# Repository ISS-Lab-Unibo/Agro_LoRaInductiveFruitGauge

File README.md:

# Agro LoRa Inductive Fruit Gauge

An open-source, low-cost and low-power LoRaWAN sensor node for continuous, non-destructive monitoring of fruit growth directly on the tree, together with the high-resolution inductive fruit gauges (*pliers*) it reads.

## Overview

Fruits shrink and swell every day following the plant's water balance. Tracking these sub-millimetre variations makes it possible to detect water stress, to time irrigation and to follow fruit development during the season. This needs sensors that are accurate, cheap enough to be deployed in large numbers, and able to run for months without anybody touching them.

The system has two parts:

| Part | What it does |
| ---- | ------------ |
| **Inductive fruit gauge** (plier) | A two-arm caliper built from FR4 PCBs. A contactless inductive angle sensor (Microchip LX3302A) measures the opening angle of the arms, from which the fruit diameter is computed. An on-board LMT01 sensor measures the plier temperature for thermal compensation. Data are sent digitally over the automotive **SENT** protocol. |
| **Sensor node** | A LoRaWAN hub based on the RAKwireless RAK3172-SiP (STM32WLE5JC). It powers and reads up to **8 fruit gauges** and **4 analog sensors**, applies calibration and thermal compensation locally, and sends the results over LoRaWAN. It runs from a Li-ion battery recharged by a small solar panel. |

To the best of the authors' knowledge, this is the first sensor node to bring the SENT protocol into agricultural applications, so that low-cost automotive sensors can be used in the orchard.

## Key specifications

**Fruit gauge**

| Parameter | Value |
| --------- | ----- |
| Sensing principle | Inductive angular sensing (planar coils on FR4 + copper target), Microchip LX3302A |
| Measurement range | up to 120 mm fruit diameter |
| Nominal resolution | 71 µm (1 LSB) |
| Accuracy after calibration | mean absolute error 111 µm, maximum error < 247 µm (cubic-spline calibration, 33 points) |
| Temperature sensor | Texas Instruments LMT01 (pulse-count output) |
| Output | SENT (tick = 24 µs) + temperature pulse train |
| Supply | 5 V, switched on by the node only during the reading |
| Weight | about 81 g |
| Structure | FR4 PCBs used as both circuit and mechanical frame, PTFE spacers, 3D-printed PETG clips |

**Sensor node**

| Parameter | Value |
| --------- | ----- |
| MCU / radio | RAK3172-SiP: STM32WLE5JC (Arm Cortex-M4, 48 MHz, 256 kB Flash, 64 kB RAM) + SX126x-class LoRa radio |
| Network | LoRaWAN, EU868, ABP activation, application port 2 |
| Fruit gauge inputs | 8 (4-pin Molex PicoBlade), individually powered |
| Analog inputs | 4 × 0–3.3 V (3-pin Molex PicoBlade), with a switched 3.3 V supply |
| Energy harvesting | TI BQ25570 with MPPT for a photovoltaic cell, Li-ion battery, 3.3 V buck output |
| Configuration | USB-C (CH340E USB–UART bridge) and the desktop app in [`Configuring software`](Configuring%20software) |
| PCB | 6-layer, 1.6 mm |
| Cost | about €25 per node (€24.92 for a batch of 20) |
| Battery life without sun | 1440 h (60 days) with 4 gauges, 1156 h (48 days) with 8 gauges, 800 mAh battery, 300 s interval; up to 2602 h (108 days) with the battery-aware sampling interval |

## How it works

1. **Wake-up.** The RTC wakes the MCU from Stop 2 mode at the end of each acquisition interval.
2. **Fruit gauge readings.** The node turns on the 5 V boost converter, then powers one gauge at a time through its load switch. For each gauge it averages a configurable number of SENT frames and reads the LMT01 temperature. SENT and temperature lines are selected with two 8:1 multiplexers and decoded in firmware with timer input capture, since the MCU has no SENT peripheral.
3. **Analog readings.** The analog sensors' 3.3 V supply is turned on. After a configurable pre-sampling time, each enabled input is sampled and averaged by the 12-bit ADC.
4. **Computation.** Each raw reading is converted to an opening angle with a cubic-spline calibration. The diameter is then computed as `d = 2·L·sin(α/2)` and corrected for the thermal expansion of the FR4 arms and the PETG clips.
5. **Transmission.** A 26-byte LoRaWAN uplink is sent. The node then turns off every power stage and goes back to sleep.

When the battery voltage is low, the node increases its sampling interval to extend its lifetime (in firmware v1.0.0, up to 3× between 3.85 V and 3.65 V). Below 3.65 V it skips the readings.

More details, including the power budget of each phase, are given in the papers below and in the [`Firmware`](Firmware) documentation.

## Repository contents

| Folder / file | Contents |
| ------------- | -------- |
| [`building_instructions.md`](building_instructions.md) | **Step-by-step guide to build the system**: materials, PCB ordering, programming, mechanical assembly, wiring and first start-up. |
| [`Schematics and Gerbers`](Schematics%20and%20Gerbers) | KiCad projects, PDF schematics, Gerbers, BOM and pick-and-place files for the sensor node and the fruit gauge. |
| [`Firmware`](Firmware) | STM32CubeIDE project of the node, ready-to-flash `.hex`, LX3302A configuration file and ChirpStack payload decoder. |
| [`Configuring software`](Configuring%20software) | PyQt6 desktop app to configure the node over USB (Python sources and a Windows executable). |
| [`3d models`](3d%20models) | FreeCAD/STEP/STL models of the fruit gauge, 3D-printable clips and PTFE spacer geometries (STL/SVG/G-code). |
| [`Images`](Images) | Pictures used in the documentation. |

## Getting started

1. Read the [building instructions](building_instructions.md) and collect the parts.
2. Order the PCBs from the [`Schematics and Gerbers`](Schematics%20and%20Gerbers) folder.
3. Flash the node with the `.hex` file and program every LX3302A with `lx3302a_config.txt` (see [`Firmware`](Firmware)).
4. Assemble the fruit gauges and connect them to the node.
5. Set the LoRaWAN keys and the acquisition parameters with the [configuration software](Configuring%20software).
6. Add the [ChirpStack decoder](Firmware/Chirpstack_decoder.js) to your network server and install the node in the orchard.

## Publications

If you use this project in your research, please cite:

> L. M. Peppi, A. Gallo, L. Manfrini, and L. De Marchi,
> "Inductive Sensor for Real-Time, Autonomous and Non-Destructive Fruit Size and Growth Monitoring,"
> *2025 IEEE International Workshop on Metrology for Agriculture and Forestry (MetroAgriFor)*, pp. 29–34, 2025.
> [IEEE Xplore](https://ieeexplore.ieee.org/document/11512426) | [DOI: 10.1109/MetroAgriFor66923.2025.11512426](https://doi.org/10.1109/MetroAgriFor66923.2025.11512426)

This paper covers the design and metrological characterisation of the inductive fruit gauge: coil design, temperature behaviour, non-linearity calibration and thermal compensation.

> L. M. Peppi, L. Manfrini, and L. De Marchi,
> "An Open-Source, Low-Cost and Low-Power LoRaWAN Hub for SENT-Based Fruit Growth and Analog Plant Related Physiological Sensors,"
> *2026 IEEE International Workshop on Metrology for Agriculture and Forestry (MetroAgriFor)*, 2026.

This paper covers the sensor node: architecture, SENT decoding over long cables, operating modes and energy budget.

Earlier versions of the fruit gauge (potentiometer-based) are described in:

* L. M. Peppi *et al.*, "A low-cost and high-accuracy non-invasive system for the monitoring of fruit growth," *IEEE MetroAgriFor 2020*, pp. 18–23.
* L. M. Peppi *et al.*, "Low-cost, high-resolution and no-manning distributed sensing system for the continuous monitoring of fruit growth in precision farming," *Acta IMEKO*, vol. 12, no. 2, pp. 1–11, 2023.

## Authors

Developed at the University of Bologna by the [ISS Lab](https://github.com/ISS-Lab-Unibo) (DEI, ARCES) and the [ECOPOM](https://github.com/ECOPOM) group (DISTAL):

* Lorenzo Mistral Peppi — DEI, ARCES
* Alessandro Gallo — CIRI-MAM
* Luigi Manfrini — DISTAL, ARCES
* Luca De Marchi — DEI, ARCES

## Acknowledgements

This work was carried out within the Emilia-Romagna Regional Programme — European Regional Development Fund (ERDF/FESR) 2021–2027, Priority 1, Specific Objective 1.1, Action 1.1.2 — Call for Strategic Industrial Research Projects — Project *"Smart Specialized Sustainable Stonefruit Orchard"*.

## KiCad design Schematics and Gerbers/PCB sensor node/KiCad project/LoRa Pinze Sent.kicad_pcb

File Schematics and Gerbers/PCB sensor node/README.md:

# Sensor Node PCB

Design and production files of the LoRaWAN sensor node, internally called *LoRa Pinze Sent*, V1.1.

| Folder / file | Contents |
| ------------- | -------- |
| `KiCad project/` | KiCad 10 project (`LoRa Pinze Sent.kicad_pro`), hierarchical schematic and 6-layer layout |
| `LoRa pinze Sent V1.1 schematic.pdf` | PDF schematic |
| `Gerber production files/` | `GERBER-LoRa Pinze Sent.zip`, `BOM-LoRa Pinze Sent.csv`, `CPL-LoRa Pinze Sent.csv` |

## Architecture

<!-- TODO: add the block diagram (Fig. 1 of the MetroAgriFor 2026 paper) to Images/ and reference it here. -->

| Block | Main parts | Function |
| ----- | ---------- | -------- |
| MCU + radio | RAK3172-SiP (STM32WLE5JC + SX126x) | Acquisition, processing, LoRaWAN. RF output on U.FL (J4) through a matching network |
| Energy harvesting | TI BQ25570, L4/L5 | MPPT solar charger for the Li-ion battery and 3.3 V buck output. Battery-OK thresholds ≈ 3.32 V / 3.60 V; the buck is turned off below the lower one to prevent deep discharge. Max. battery voltage ≈ 4.23 V |
| RTC backup | VL-1220 rechargeable coin cell (BT1), JP4 | Keeps the RTC (VBAT pin) running |
| Fruit gauge supply | TPS61322 (5 V boost), TPS22917 load switches (one per gauge, plus stage switches) | 5 V is generated only during readings, then switched to each gauge on its own |
| Gauge power control | TCA9534 I²C expander (address 0x20) | Drives the 8 per-gauge load switches. Its pins default to inputs at power-on, so all gauges start off |
| Gauge inputs | 2 × SN74HCS151 8:1 mux, 12k/22k dividers, BAV199 | One mux for the SENT lines, one for the temperature lines. The 5 V signals are divided down to ≈ 3.2 V and clamped |
| Analog inputs | TMUX1204 4:1 mux, TPS22917, BAV199, 10 Ω | 4 × 0–3.3 V inputs with a switched 3.3 V sensor supply |
| Battery sensing | TPS22917 + 200k/200k divider + RC filter | Divider connected only during the measurement (wait > 5 τ before sampling) |
| USB / configuration | USB-C (GT-USB-7055BB), USBLC6-2 ESD, CH340E, NCP115 LDO, TMUX1219 ×3 | USB-to-UART bridge powered from USB. The analog switches isolate the UART/RTS lines when USB is not connected, to avoid leakage |
| User interface | LED1 (PB11), LED2 (USB), USER button B1 (PA7), RESET button B2 | |

## Connectors

| Ref | Type | Pinout |
| --- | ---- | ------ |
| J9–J16 | Molex PicoBlade 53398-0471 (4-pin) — fruit gauges 1–8 | 1 GND · 2 Temperature · 3 SENT · 4 +5 V switched |
| J5–J8 | Molex PicoBlade 53398-0371 (3-pin) — analog inputs 4–1 | 1 +3.3 V switched · 2 Analog in · 3 GND |
| J2 | JST PH B2B-PH-K-S — battery | 1 +VBAT · 2 GND |
| J3 | 2-pin — solar panel | 1 +Solar · 2 GND |
| J17 | USB-C | Configuration (CH340E) |
| CN1 | 6-pin — SWD | 1 VDD · 2 SWCLK · 3 GND · 4 SWDIO · 5 NRST · 6 NC |
| J1 | 3-pin — debug UART | 1 RX (PA3) · 2 TX (PA2) · 3 GND |
| J4 | U.FL | LoRa antenna |

Channel mapping: gauge *n* (1–8) → J(8+*n*); analog input 1 → J8, 2 → J7, 3 → J6, 4 → J5.

## MCU pin assignment

| Pin | Net | Function |
| --- | --- | -------- |
| PB8 | `SENTInput` | SENT input (from SENT mux) |
| PB9 | `TempDgitalOutput` | LMT01 pulse input (from temperature mux) |
| PC0 / PC1 / PC2 | `CTRLA/B/C` | Gauge mux select |
| PA10 | `PinzeOn` | Gauge stage power enable |
| PB14 | `BoostOnPinze` | 5 V boost enable |
| PA11 / PA12 | `I2C1_SDA` / `I2C1_SCL` | TCA9534 expander |
| PB1 | `AnalogIN` | ADC input (from analog mux) |
| PA8 / PA9 | `AnSel0` / `AnSel1` | Analog mux select |
| PB2 | `AnalogPowerIN` | Analog sensor supply enable |
| PB12 | `VStorageReadActivate` | Battery divider enable |
| PB13 | `VStorageSensing` | Battery voltage ADC input |
| PA2 / PA3 | `USART2_TX` / `USART2_RX` | Configuration / debug UART |
| PA5 / PA6 | `CTS#` / `RTS#` | CH340E handshake (RTS wakes the MCU) |
| PA7 | `BlueButton` | USER button |
| PB11 | `indicatore` | Status LED |
| PA13 / PA14 | `SWDIO` / `SWCLK` | Debug |

## Schematic sheets

| Sheet | File |
| ----- | ---- |
| Top level (MCU, connectors, buttons, LEDs) | `LoRa Pinze Sent.kicad_sch` |
| Energy harvesting (BQ25570) | `untitled.kicad_sch` (`power_supply1`) |
| Battery sensing | `Avoir.kicad_sch` |
| Gauge supply and I²C expander | `AlimentazionePinze.kicad_sch` → `SwitchPowerPinze.kicad_sc.kicad_sch` (×8) |
| Gauge input muxes | `DigitalInputMux.kicad_sch` → `DigitalInput.kicad_sch` (×8) |
| Analog inputs | `InputAnalogico.kicad_sch` |
| USB–UART | `USB_Uart.kicad_sch` |
| Antenna and matching network | `antennas.kicad_sch` |

## Manufacturing

Upload `GERBER-LoRa Pinze Sent.zip` to the PCB manufacturer (6 layers, 1.6 mm), then use the BOM and CPL files for assembly. Through-hole and mechanical parts that the assembler does not mount (battery/solar/coin-cell connectors, headers) are soldered by hand.

About €25 per node for a batch of 20.

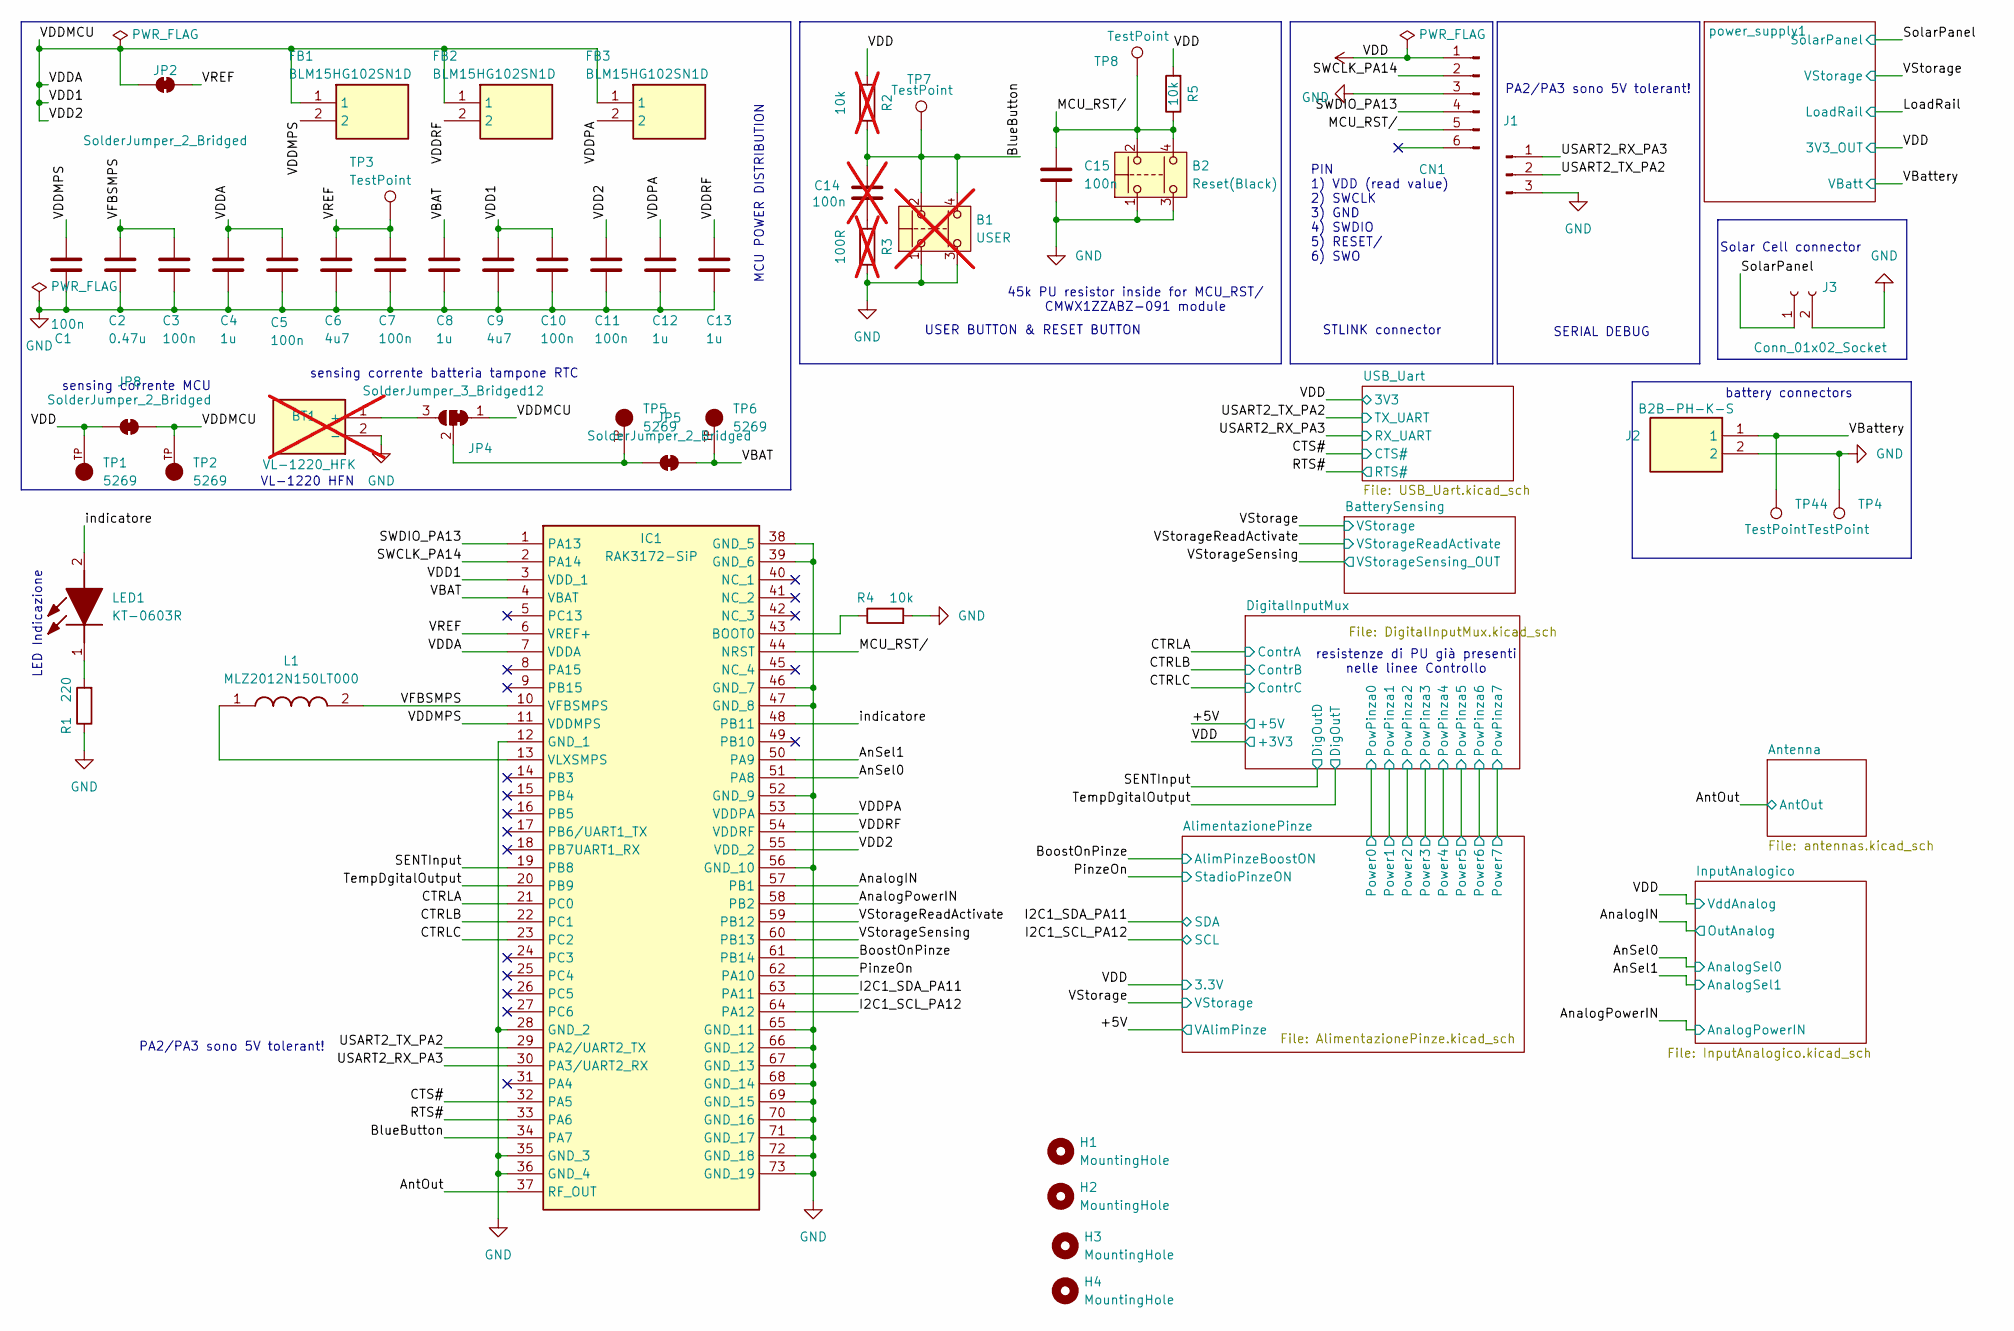
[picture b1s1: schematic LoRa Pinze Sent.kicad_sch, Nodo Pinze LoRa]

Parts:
B1: USER; TS046655BK160SMT; LCSC C5340119; not fitted
B2: Reset(Black); TS046655BK160SMT; LCSC C5340119
BT1: VL-1220_HFK; VL1220HFK; Manufacturer_Part_Number VL-1220/HFK; not fitted
C1, C3, C5, C7, C10, C11, C15: 100n; C_0402_1005Metric_Pad0.74x0.62mm_HandSolder; LCSC C1525
C2: 0.47u; C_0603_1608Metric_Pad1.08x0.95mm_HandSolder; LCSC C1623
C4, C8, C12, C13: 1u; C_0402_1005Metric_Pad0.74x0.62mm_HandSolder; LCSC C52923
C6, C9: 4u7; C_0402_1005Metric_Pad0.74x0.62mm_HandSolder; LCSC C23733
C14: 100n; C_0402_1005Metric_Pad0.74x0.62mm_HandSolder; LCSC C1525; not fitted
CN1: Conn_01x06_Pin; PinSocket_1x06_P2.54mm_Vertical
FB1, FB2, FB3: BLM15HG102SN1D; NFZ15SG152SN10B; Manufacturer_Part_Number BLM15HG102SN1D; Mouser Part Number 81-BLM15HG102SN1D
H1, H2, H3, H4: MountingHole; MountingHole_3.2mm_M3
IC1: RAK3172-SiP; RAK3172SiP; Manufacturer_Part_Number RAK3172-SiP; LCSC C19818882
J1: Conn_01x03_Pin; PinHeader_1x03_P2.54mm_Vertical
J2: B2B-PH-K-S; SHDR2W50P0X200_1X2_590X450X600P; Manufacturer_Part_Number B2B-PH-K-S
J3: Conn_01x02_Socket; Samtec_HPM-02-05-x-S_Straight_1x02_Pitch5.08mm
JP2, JP5, JP8: SolderJumper_2_Bridged; SolderJumper-2_P1.3mm_Bridged_RoundedPad1.0x1.5mm
JP4: SolderJumper_3_Bridged12; SolderJumper-3_P1.3mm_Bridged12_RoundedPad1.0x1.5mm
L1: MLZ2012N150LT000; INDC2012X105N; Manufacturer_Part_Number MLZ2012N150LT000; Mouser Part Number 810-MLZ2012N150LT000
LED1: KT-0603R; LEDC1608X70N; Manufacturer_Part_Number KT-0603R; LCSC C2286
R1: 220; R_0402_1005Metric_Pad0.72x0.64mm_HandSolder; LCSC C25091
R2: 10k; R_0402_1005Metric; LCSC C25744; not fitted
R3: 100R; R_0402_1005Metric; LCSC C25076; not fitted
R4, R5: 10k; R_0402_1005Metric; LCSC C25744
TP1, TP2, TP5, TP6: 5269; KEYSTONE_5269; PARTREV H
TP3, TP4, TP7, TP8, TP44: TestPoint; TestPoint_Pad_1.0x1.0mm

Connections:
/AnSel0: IC1.51 (PA8); also elsewhere on the board
/AnSel1: IC1.50 (PA9); also elsewhere on the board
/AnalogIN: IC1.57 (PB1); also elsewhere on the board
/AnalogPowerIN: IC1.58 (PB2); also elsewhere on the board
/AntOut: IC1.37 (RF_OUT); also elsewhere on the board
/BlueButton: B1.2, B1.4, C14.1, IC1.34 (PA7), R2.1, TP7.1 (1_1)
/BoostOnPinze: IC1.61 (PB14); also elsewhere on the board
/CTRLA: IC1.21 (PC0); also elsewhere on the board
/CTRLB: IC1.22 (PC1); also elsewhere on the board
/CTRLC: IC1.23 (PC2); also elsewhere on the board
/CTS#: IC1.32 (PA5); also elsewhere on the board
/I2C1_SCL_PA12: IC1.64 (PA12); also elsewhere on the board
/I2C1_SDA_PA11: IC1.63 (PA11); also elsewhere on the board
/MCU_RST/: B2.2, B2.4, C15.1, CN1.5, IC1.44 (NRST), R5.1, TP8.1 (1_1)
/PinzeOn: IC1.62 (PA10); also elsewhere on the board
/RTS#: IC1.33 (PA6); also elsewhere on the board
/SENTInput: IC1.19 (PB8); also elsewhere on the board
/SWCLK_PA14: CN1.2, IC1.2 (PA14)
/SWDIO_PA13: CN1.4, IC1.1 (PA13)
/SolarPanel: J3.1; also elsewhere on the board
/TempDgitalOutput: IC1.20 (PB9); also elsewhere on the board
/USART2_RX_PA3: IC1.30 (PA3/UART2_RX), J1.1; also elsewhere on the board
/USART2_TX_PA2: IC1.29 (PA2/UART2_TX), J1.2; also elsewhere on the board
/VBAT: C8.1, IC1.4 (VBAT), JP5.1 (A), TP6.TP
/VBattery: J2.1, TP44.1 (1_1); also elsewhere on the board
/VDD1: C4.1, C5.1, C9.1, C10.1, C11.1, FB1.1, FB2.1, FB3.1, IC1.3 (VDD_1), IC1.7 (VDDA), IC1.55 (VDD_2), JP2.1 (A), JP4.1 (A), JP8.1 (A), TP2.TP
/VDDMPS: C1.1, FB1.2, IC1.11 (VDDMPS)
/VDDPA: C12.1, FB3.2, IC1.53 (VDDPA)
/VDDRF: C13.1, FB2.2, IC1.54 (VDDRF)
/VFBSMPS: C2.1, C3.1, IC1.10 (VFBSMPS), L1.2
/VREF: C6.1, C7.1, IC1.6 (VREF+), JP2.2 (B), TP3.1 (1_1)
/VStorageReadActivate: IC1.59 (PB12); also elsewhere on the board
/VStorageSensing: IC1.60 (PB13); also elsewhere on the board
/indicatore: IC1.48 (PB11), LED1.2 (A)
GND: B1.1, B1.3, B2.1, B2.3, BT1.2 (-), C1.2, C2.2, C3.2, C4.2, C5.2, C6.2, C7.2, C8.2, C9.2, C10.2, C11.2, C12.2, C13.2, C15.2, CN1.3, IC1.12 (GND_1), IC1.28 (GND_2), IC1.35 (GND_3), IC1.36 (GND_4), IC1.38 (GND_5), IC1.39 (GND_6), IC1.46 (GND_7), IC1.47 (GND_8), IC1.52 (GND_9), IC1.56 (GND_10), IC1.65 (GND_11), IC1.66 (GND_12), IC1.67 (GND_13), IC1.68 (GND_14), IC1.69 (GND_15), IC1.70 (GND_16), IC1.71 (GND_17), IC1.72 (GND_18), IC1.73 (GND_19), J1.3, J2.2, J3.2, R1.1, R3.1, R4.2, TP4.1 (1_1); also elsewhere on the board
unnamed: BT1.1 (+), JP4.3 (B)
unnamed: C14.2, R3.2
unnamed: IC1.43 (BOOT0), R4.1
unnamed: IC1.13 (VLXSMPS), L1.1
unnamed: JP4.2 (C), JP5.2 (B), TP5.TP
unnamed: LED1.1 (K), R1.2
VDD_MCU_LRA: CN1.1, JP8.2 (B), R2.2, R5.2, TP1.TP; also elsewhere on the board

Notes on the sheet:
Solar Cell connector
PA2/PA3 sono 5V tolerant!
45k PU resistor inside for MCU_RST/ CMWX1ZZABZ-091 module
sensing corrente batteria tampone RTC
SERIAL DEBUG
battery connectors
resistenze di PU già presenti nelle linee Controllo
STLINK connector
PIN 1) VDD (read value) 2) SWCLK 3) GND 4) SWDIO 5) RESET/ 6) SWO
VL-1220 HFN
sensing corrente MCU
MCU POWER DISTRIBUTION
LED Indicazione
USER BUTTON & RESET BUTTON

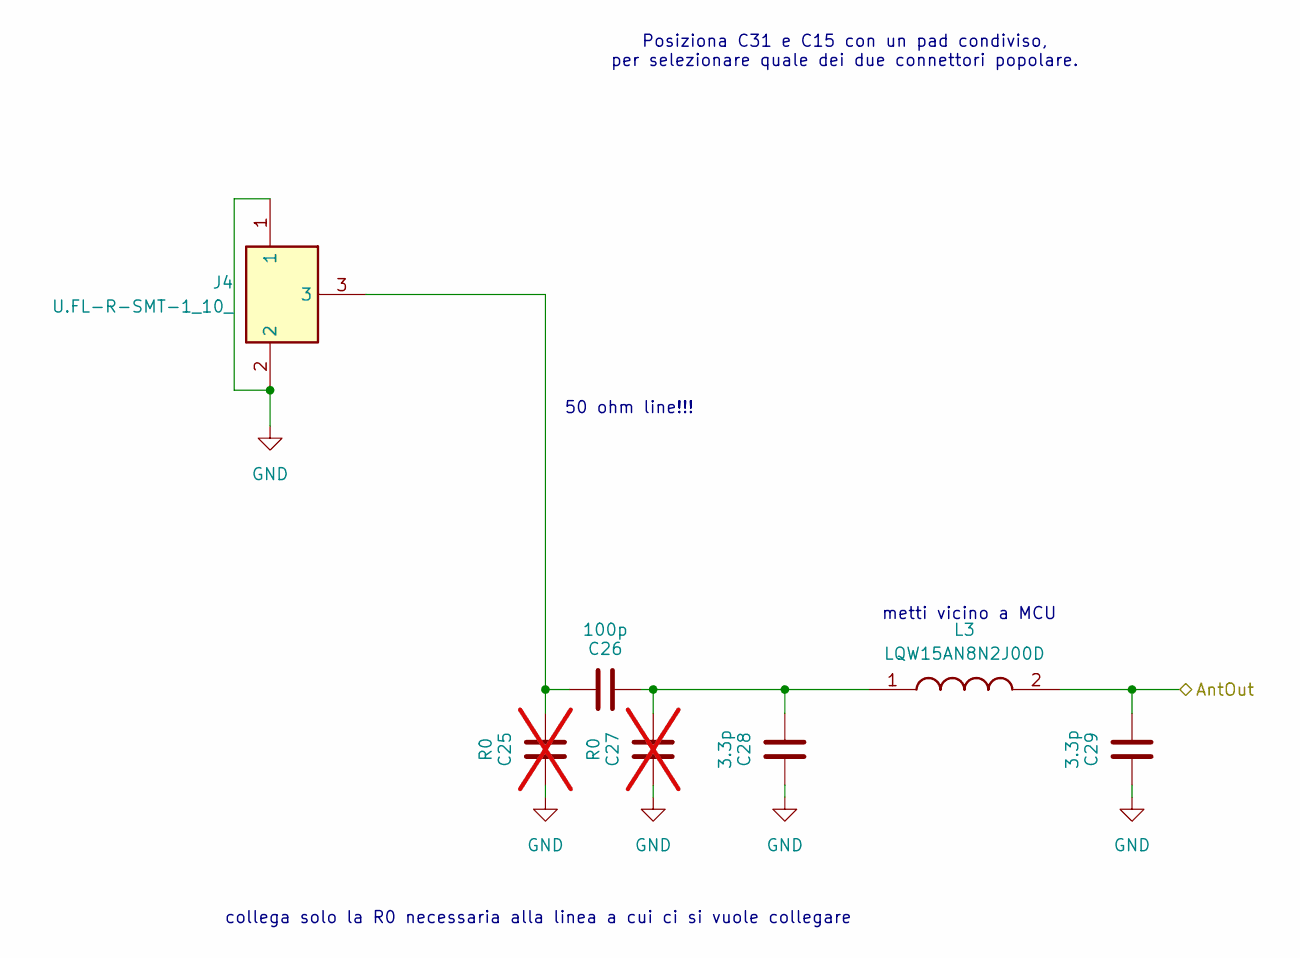
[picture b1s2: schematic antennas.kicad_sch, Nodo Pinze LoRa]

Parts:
C25, C27: R0; C_0402_1005Metric_Pad0.74x0.62mm_HandSolder; not fitted
C26: 100p; C_0402_1005Metric_Pad0.74x0.62mm_HandSolder; LCSC C1546
C28, C29: 3.3p; C_0402_1005Metric_Pad0.74x0.62mm_HandSolder; LCSC C1565
J4: U.FL-R-SMT-1_10_; Manufacturer_Part_Number U.FL-R-SMT-1(10); Mouser Part Number 798-U.FL-R-SMT-110
L3: LQW15AN8N2J00D; LQW15CNR20J00B; Manufacturer_Part_Number LQW15AN8N2J00D; Mouser Part Number 81-LQW15AN8N2J00D

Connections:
/AntOut: C29.2, L3.2; also elsewhere on the board
GND: C25.1, C27.1, C28.1, C29.1, J4.1, J4.2; also elsewhere on the board
unnamed: C25.2, C26.1, J4.3
unnamed: C26.2, C27.2, C28.2, L3.1

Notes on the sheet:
metti vicino a MCU
50 ohm line!!!
collega solo la R0 necessaria alla linea a cui ci si vuole collegare
Posiziona C31 e C15 con un pad condiviso, per selezionare quale dei due connettori popolare.

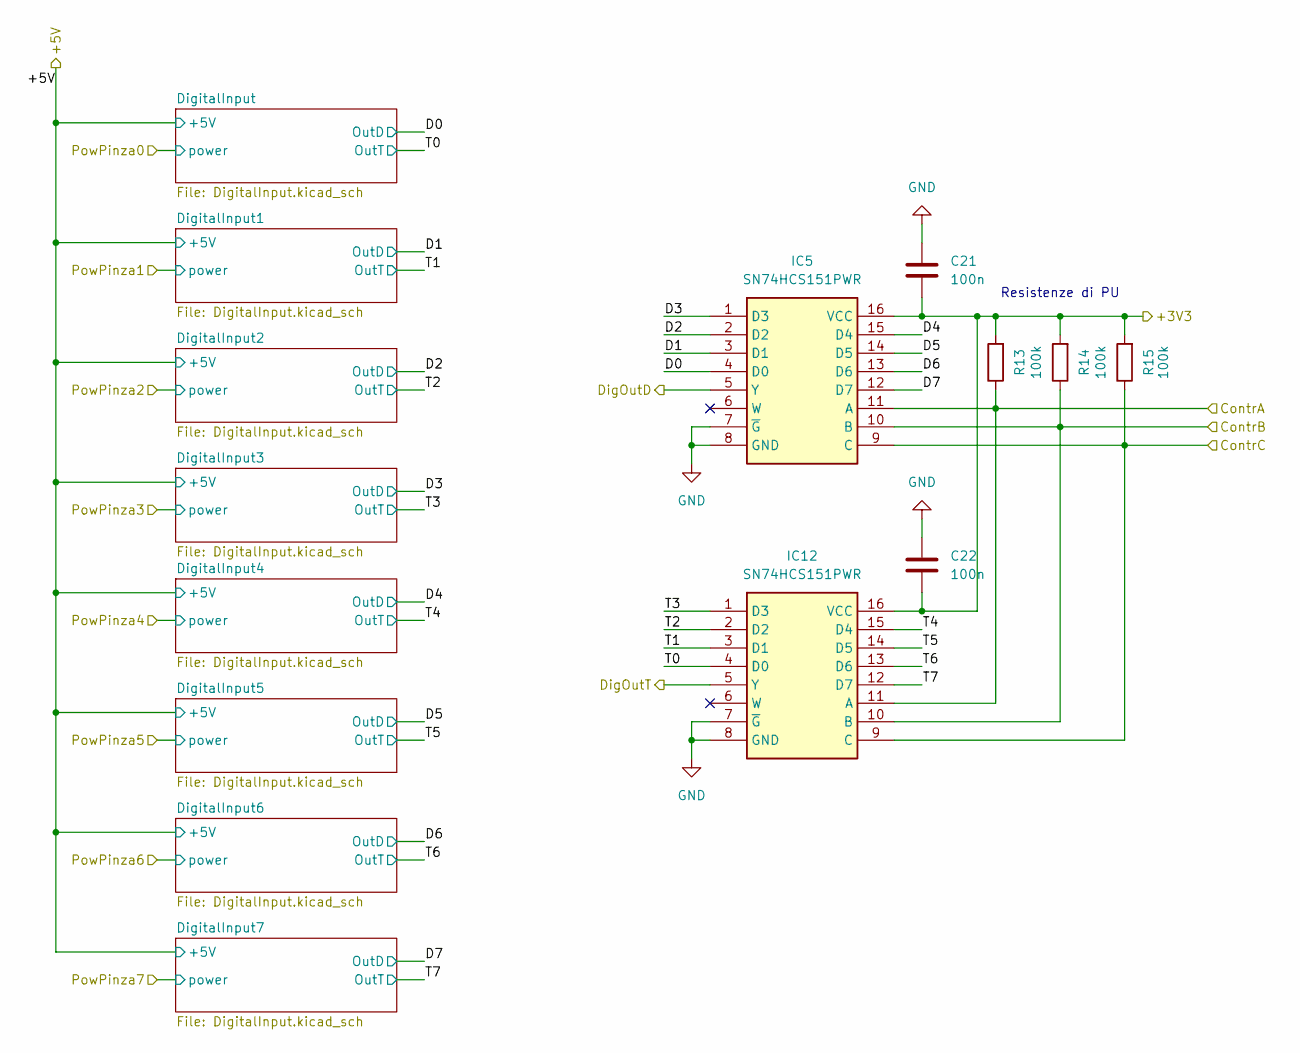
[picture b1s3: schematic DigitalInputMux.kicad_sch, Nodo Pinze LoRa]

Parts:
C21, C22: 100n; C_0402_1005Metric_Pad0.74x0.62mm_HandSolder; LCSC C1525
IC5, IC12: SN74HCS151PWR; SOP65P640X120-16N; Manufacturer_Part_Number SN74HCS151PWR; Mouser Part Number 595-SN74HCS151PWR
R13, R14, R15: 100k; R_0402_1005Metric; LCSC C25741

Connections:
/CTRLA: IC5.11 (A), IC12.11 (A), R13.1; also elsewhere on the board
/CTRLB: IC5.10 (B), IC12.10 (B), R14.1; also elsewhere on the board
/CTRLC: IC5.9 (C), IC12.9 (C), R15.1; also elsewhere on the board
/DigitalInputMux/D0: IC5.4 (D0); also elsewhere on the board
/DigitalInputMux/D1: IC5.3 (D1); also elsewhere on the board
/DigitalInputMux/D2: IC5.2 (D2); also elsewhere on the board
/DigitalInputMux/D3: IC5.1 (D3); also elsewhere on the board
/DigitalInputMux/D4: IC5.15 (D4); also elsewhere on the board
/DigitalInputMux/D5: IC5.14 (D5); also elsewhere on the board
/DigitalInputMux/D6: IC5.13 (D6); also elsewhere on the board
/DigitalInputMux/D7: IC5.12 (D7); also elsewhere on the board
/DigitalInputMux/T0: IC12.4 (D0); also elsewhere on the board
/DigitalInputMux/T1: IC12.3 (D1); also elsewhere on the board
/DigitalInputMux/T2: IC12.2 (D2); also elsewhere on the board
/DigitalInputMux/T3: IC12.1 (D3); also elsewhere on the board
/DigitalInputMux/T4: IC12.15 (D4); also elsewhere on the board
/DigitalInputMux/T5: IC12.14 (D5); also elsewhere on the board
/DigitalInputMux/T6: IC12.13 (D6); also elsewhere on the board
/DigitalInputMux/T7: IC12.12 (D7); also elsewhere on the board
/SENTInput: IC5.5 (Y); also elsewhere on the board
/TempDgitalOutput: IC12.5 (Y); also elsewhere on the board
GND: C21.1, C22.1, IC5.7 (~G), IC5.8 (GND), IC12.7 (~G), IC12.8 (GND); also elsewhere on the board
VDD_MCU_LRA: C21.2, C22.2, IC5.16 (VCC), IC12.16 (VCC), R13.2, R14.2, R15.2; also elsewhere on the board

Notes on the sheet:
Resistenze di PU

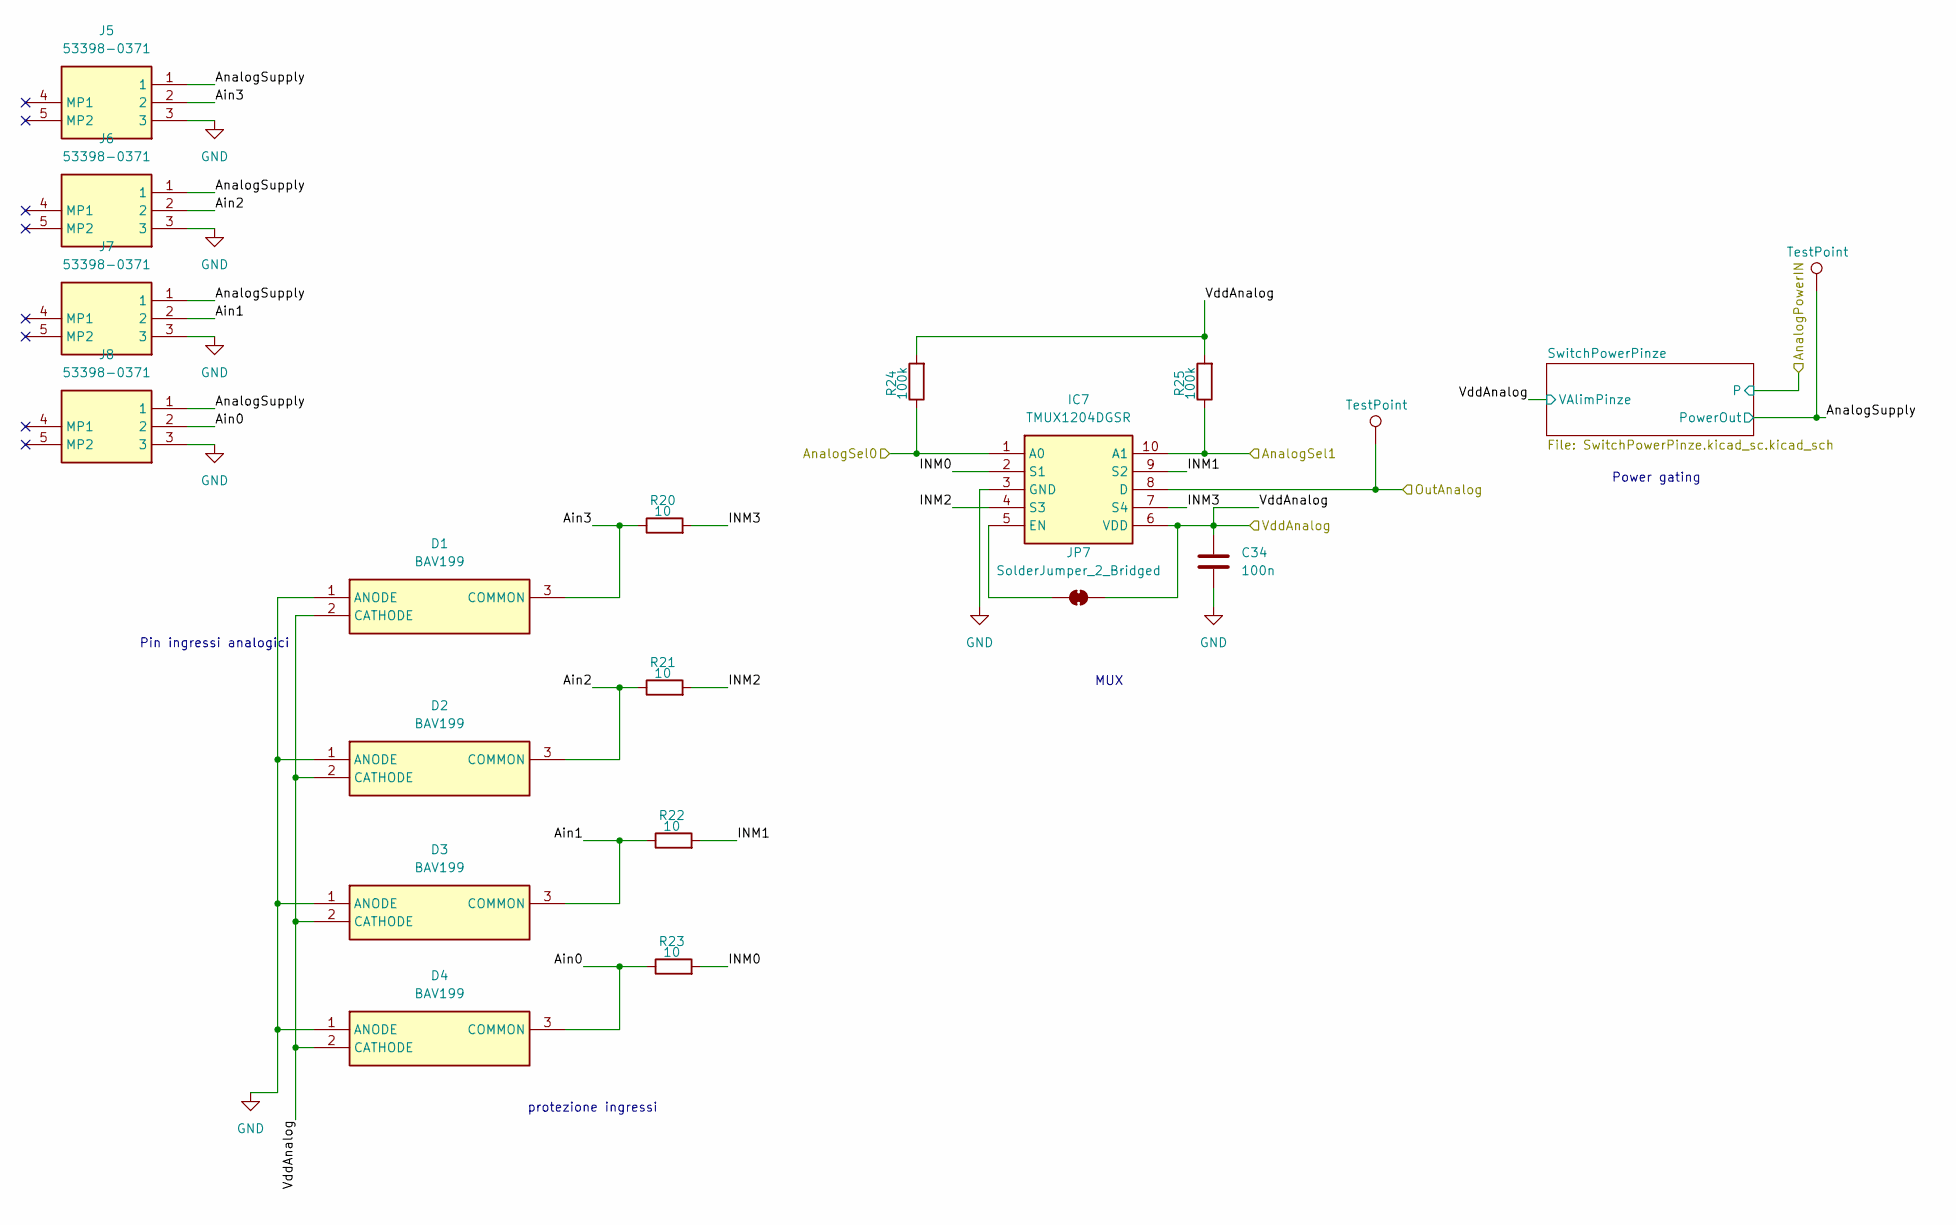
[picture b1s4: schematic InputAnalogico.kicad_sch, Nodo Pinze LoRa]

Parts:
C34: 100n; C_0402_1005Metric_Pad0.74x0.62mm_HandSolder; LCSC C1525
D1, D2, D3, D4: BAV199; SOT95P230X100-3N; Manufacturer_Part_Number BAV199; Mouser Part Number N/A
IC7: TMUX1204DGSR; SOP50P490X110-10N; Manufacturer_Part_Number TMUX1204DGSR; Mouser Part Number 595-TMUX1204DGSR
J5, J6, J7, J8: 53398-0371; 533980371; Manufacturer_Part_Number 53398-0371; Mouser Part Number 538-53398-0371
JP7: SolderJumper_2_Bridged; SolderJumper-2_P1.3mm_Bridged_RoundedPad1.0x1.5mm
R20, R21, R22, R23: 10; R_0402_1005Metric; LCSC C25077
R24, R25: 100k; R_0402_1005Metric; LCSC C25741
TP17, TP21: TestPoint; TestPoint_Pad_1.0x1.0mm

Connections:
/AnSel0: IC7.1 (A0), R24.1; also elsewhere on the board
/AnSel1: IC7.10 (A1), R25.1; also elsewhere on the board
/AnalogIN: IC7.8 (D), TP21.1 (1_1); also elsewhere on the board
/InputAnalogico/Ain0: D4.3 (COMMON), J8.2, R23.1
/InputAnalogico/Ain1: D3.3 (COMMON), J7.2, R22.1
/InputAnalogico/Ain2: D2.3 (COMMON), J6.2, R21.1
/InputAnalogico/Ain3: D1.3 (COMMON), J5.2, R20.1
/InputAnalogico/AnalogSupply: J5.1, J6.1, J7.1, J8.1, TP17.1 (1_1); also elsewhere on the board
/InputAnalogico/INM0: IC7.2 (S1), R23.2
/InputAnalogico/INM1: IC7.9 (S2), R22.2
/InputAnalogico/INM2: IC7.4 (S3), R21.2
/InputAnalogico/INM3: IC7.7 (S4), R20.2
GND: C34.2, D1.1 (ANODE), D2.1 (ANODE), D3.1 (ANODE), D4.1 (ANODE), IC7.3 (GND), J5.3, J6.3, J7.3, J8.3; also elsewhere on the board
unnamed: IC7.5 (EN), JP7.2 (B)
VDD_MCU_LRA: C34.1, D1.2 (CATHODE), D2.2 (CATHODE), D3.2 (CATHODE), D4.2 (CATHODE), IC7.6 (VDD), JP7.1 (A), R24.2, R25.2; also elsewhere on the board

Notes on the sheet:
Power gating
protezione ingressi
Pin ingressi analogici
MUX

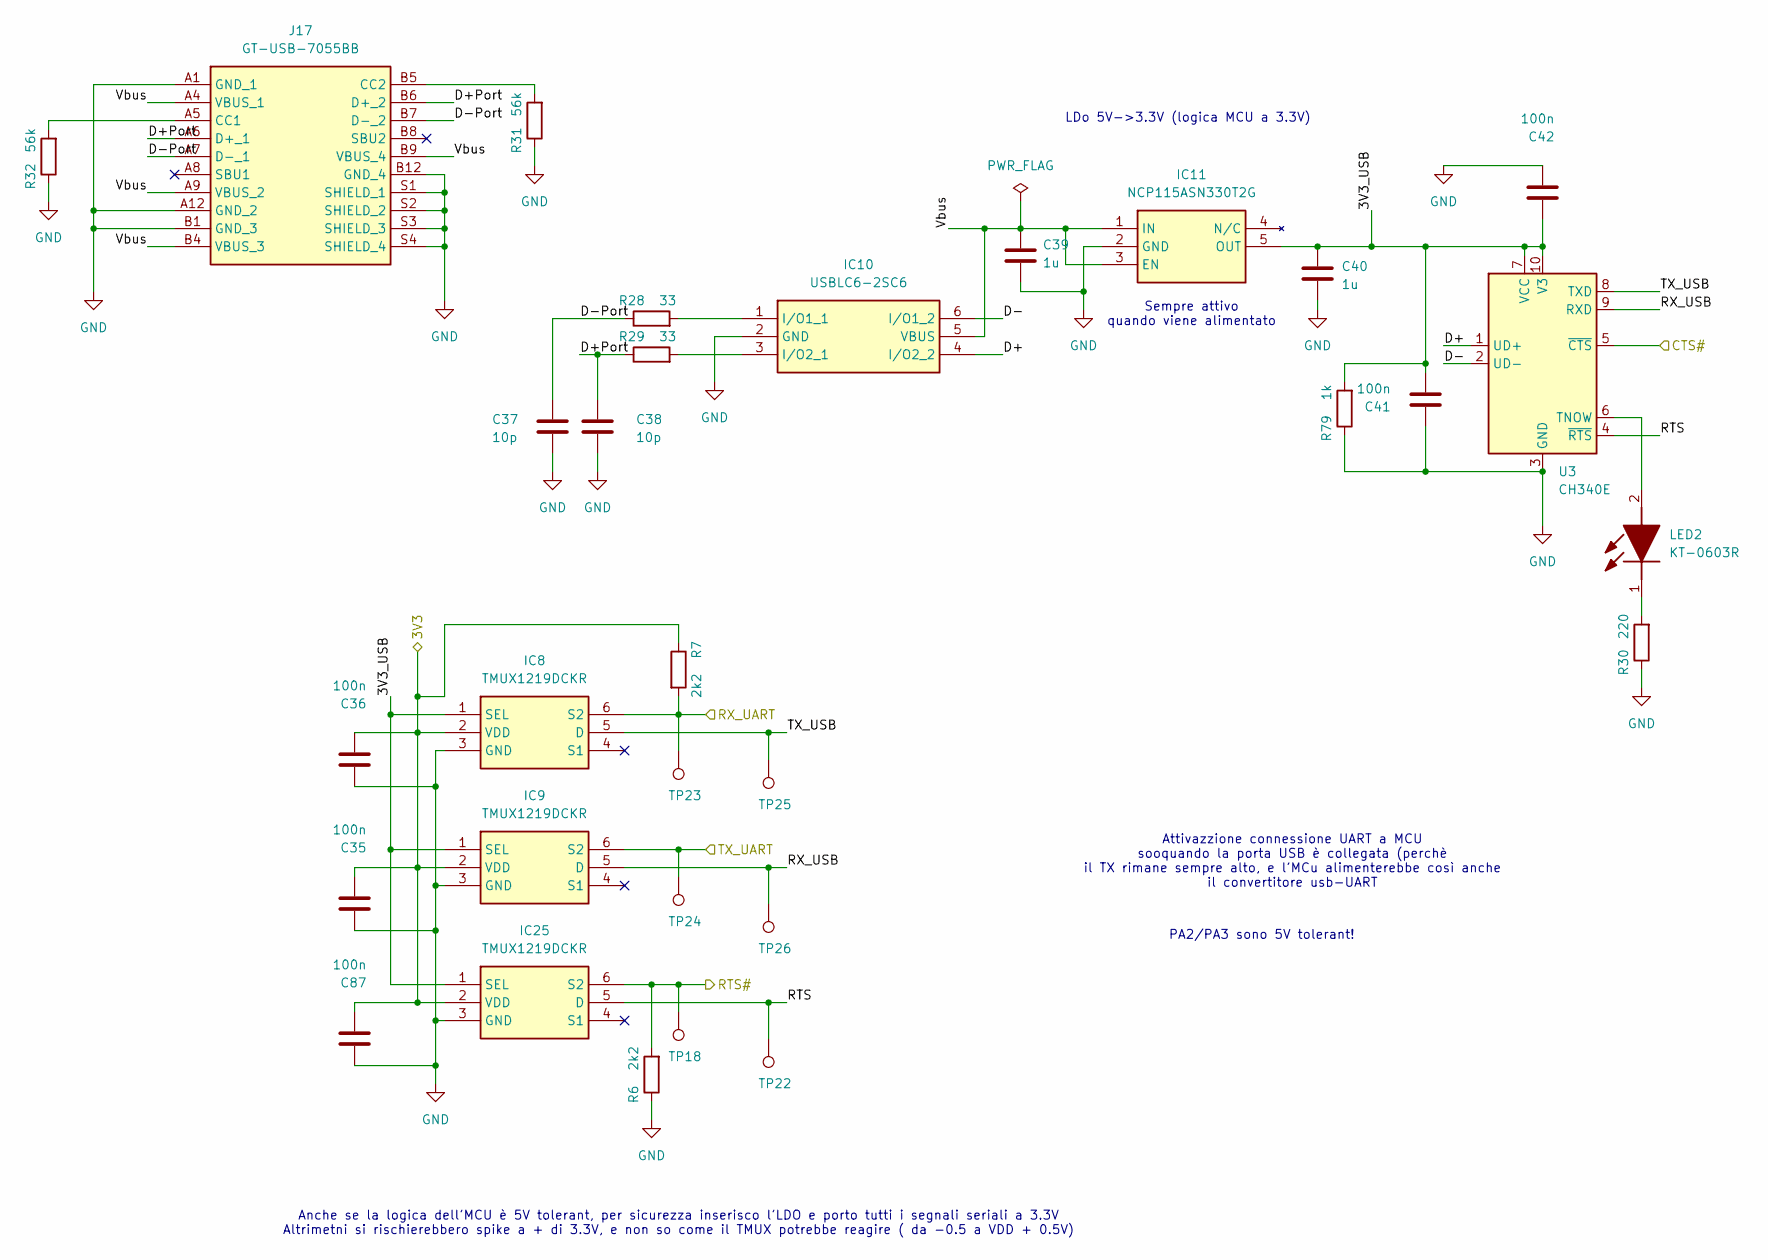
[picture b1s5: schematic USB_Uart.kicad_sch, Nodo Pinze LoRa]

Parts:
C35, C36, C41, C42, C87: 100n; C_0402_1005Metric_Pad0.74x0.62mm_HandSolder; LCSC C1525
C37, C38: 10p; C_0402_1005Metric_Pad0.74x0.62mm_HandSolder; LCSC C32949
C39, C40: 1u; C_0402_1005Metric_Pad0.74x0.62mm_HandSolder; LCSC C52923
IC8, IC9, IC25: TMUX1219DCKR; SOT65P210X110-6N; Manufacturer_Part_Number TMUX1219DCKR; Mouser Part Number 595-TMUX1219DCKR
IC10: USBLC6-2SC6; SOT95P280X145-6N; Manufacturer_Part_Number USBLC6-2SC6; Mouser Part Number 511-USBLC6-2SC6
IC11: NCP115ASN330T2G; SOT95P275X110-5N; Manufacturer_Part_Number NCP115ASN330T2G; Mouser Part Number 863-NCP115ASN330T2G
J17: GT-USB-7055BB; GTUSB7055BB; Manufacturer_Part_Number GT-USB-7055BB; LCSC C7450621
LED2: KT-0603R; LEDC1608X70N; Manufacturer_Part_Number KT-0603R; LCSC C2286
R6, R7: 2k2; R_0402_1005Metric; LCSC C25879
R28, R29: 33; R_0402_1005Metric; LCSC C25105
R30: 220; R_0402_1005Metric; LCSC C25091
R31, R32: 56k; R_0402_1005Metric; LCSC C23206
R79: 1k; R_0402_1005Metric; LCSC C11702
TP18, TP22, TP23, TP24, TP25, TP26: TestPoint; TestPoint_Pad_1.0x1.0mm
U3: CH340E; MSOP-10_3x3mm_P0.5mm; LCSC C99652

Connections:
/CTS#: U3.5 (~CTS); also elsewhere on the board
/RTS#: IC25.6 (S2), R6.2, TP18.1 (1_1); also elsewhere on the board
/USART2_RX_PA3: IC8.6 (S2), R7.2, TP23.1 (1_1); also elsewhere on the board
/USART2_TX_PA2: IC9.6 (S2), TP24.1 (1_1); also elsewhere on the board
/USB_Uart/3V3_USB: C40.1, C41.2, C42.1, IC8.1 (SEL), IC9.1 (SEL), IC11.5 (OUT), IC25.1 (SEL), R79.2, U3.7 (VCC), U3.10 (V3)
/USB_Uart/D+: IC10.4 (I/O2_2), U3.1 (UD+)
/USB_Uart/D+Port: C38.1, J17.A6 (D+_1), J17.B6 (D+_2), R29.1
/USB_Uart/D-: IC10.6 (I/O1_2), U3.2 (UD-)
/USB_Uart/D-Port: C37.1, J17.A7 (D-_1), J17.B7 (D-_2), R28.1
/USB_Uart/RTS: IC25.5 (D), TP22.1 (1_1), U3.4 (~RTS)
/USB_Uart/RX_USB: IC9.5 (D), TP26.1 (1_1), U3.9 (RXD)
/USB_Uart/TX_USB: IC8.5 (D), TP25.1 (1_1), U3.8 (TXD)
/USB_Uart/Vbus: C39.1, IC10.5 (VBUS), IC11.1 (IN), IC11.3 (EN), J17.A4 (VBUS_1), J17.A9 (VBUS_2), J17.B4 (VBUS_3), J17.B9 (VBUS_4)
GND: C35.1, C36.1, C37.2, C38.2, C39.2, C40.2, C41.1, C42.2, C87.1, IC8.3 (GND), IC9.3 (GND), IC10.2 (GND), IC11.2 (GND), IC25.3 (GND), J17.A1 (GND_1), J17.A12 (GND_2), J17.B1 (GND_3), J17.B12 (GND_4), J17.S1 (SHIELD_1), J17.S2 (SHIELD_2), J17.S3 (SHIELD_3), J17.S4 (SHIELD_4), R6.1, R30.1, R31.1, R32.1, R79.1, U3.3 (GND); also elsewhere on the board
unnamed: IC10.1 (I/O1_1), R28.2
unnamed: IC10.3 (I/O2_1), R29.2
unnamed: J17.A5 (CC1), R32.2
unnamed: J17.B5 (CC2), R31.2
unnamed: LED2.2 (A), U3.6 (TNOW)
unnamed: LED2.1 (K), R30.2
VDD_MCU_LRA: C35.2, C36.2, C87.2, IC8.2 (VDD), IC9.2 (VDD), IC25.2 (VDD), R7.1; also elsewhere on the board

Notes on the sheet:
PA2/PA3 sono 5V tolerant!
Attivazzione connessione UART a MCU sooquando la porta USB è collegata (perchè il TX rimane sempre alto, e l'MCu alimenterebbe così anche il convertitore usb-UART
Sempre attivo quando viene alimentato
LDo 5V->3.3V (logica MCU a 3.3V)
Anche se la logica dell'MCU è 5V tolerant, per sicurezza inserisco l'LDO e porto tutti i segnali seriali a 3.3V Altrimetni si rischierebbero spike a + di 3.3V, e non so come il TMUX potrebbe reagire ( da -0.5 a VDD + 0.5V)
